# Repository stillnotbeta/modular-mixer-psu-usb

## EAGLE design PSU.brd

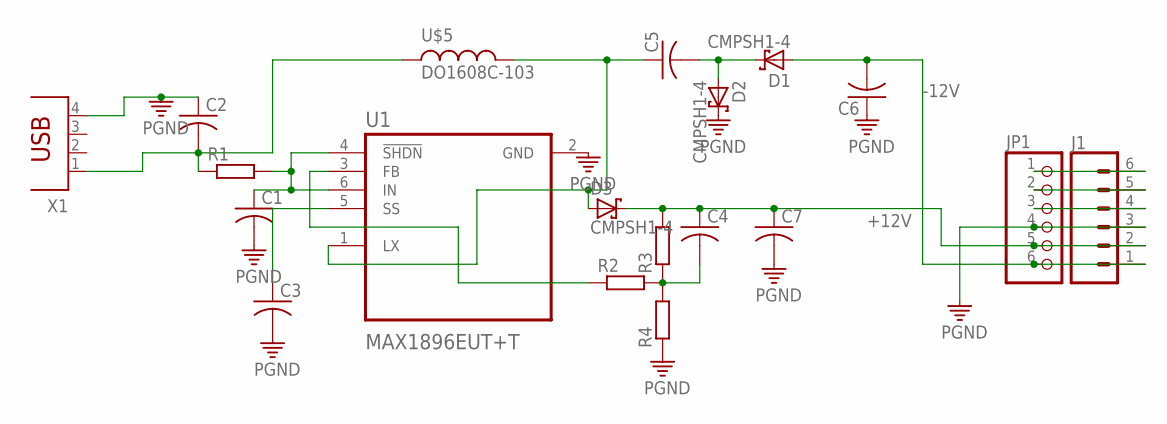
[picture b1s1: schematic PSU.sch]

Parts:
C1, C2, C3, C4, C5, C6, C7: C-US025-025X050; C025-025X050
D1, D2, D3: CMPSH1-4; SOT23
J1: CONN_06SMD-FEMALE-V2; 1X06-SMD-FEMALE
JP1: PINHD-1X6/90; 1X06/90
R1, R2, R3, R4: R-EU_0309/10; 0309/10
U1: MAX1896EUT+T; SOT95P280X145-6N
U$5: DO1608C-103; MSS1260
X1: PN61729

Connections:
+12V: C4.1, C7.1, D3.3 (C), J1.2, JP1.5, R3.2
-12V: C6.2, D1.1 (A), J1.1, JP1.6
unnamed: C1.1, R1.2, U1.4 (!SHDN), U1.6 (IN)
unnamed: C4.2, R2.2, R3.1, R4.2
unnamed: C2.2, R1.1, U$5.P$2, X1.1
unnamed: R2.1, U1.3 (FB)
unnamed: C5.1, D3.1 (A), U1.1 (LX), U$5.P$1
unnamed: C5.2, D1.3 (C), D2.1 (A)
unnamed: J1.4, JP1.3
unnamed: J1.5, JP1.2
unnamed: C3.1, U1.5 (SS)
unnamed: J1.6, JP1.1
PGND: C1.2, C2.1, C3.2, C6.1, C7.2, D2.3 (C), J1.3, JP1.4, R4.1, U1.2 (GND), X1.4

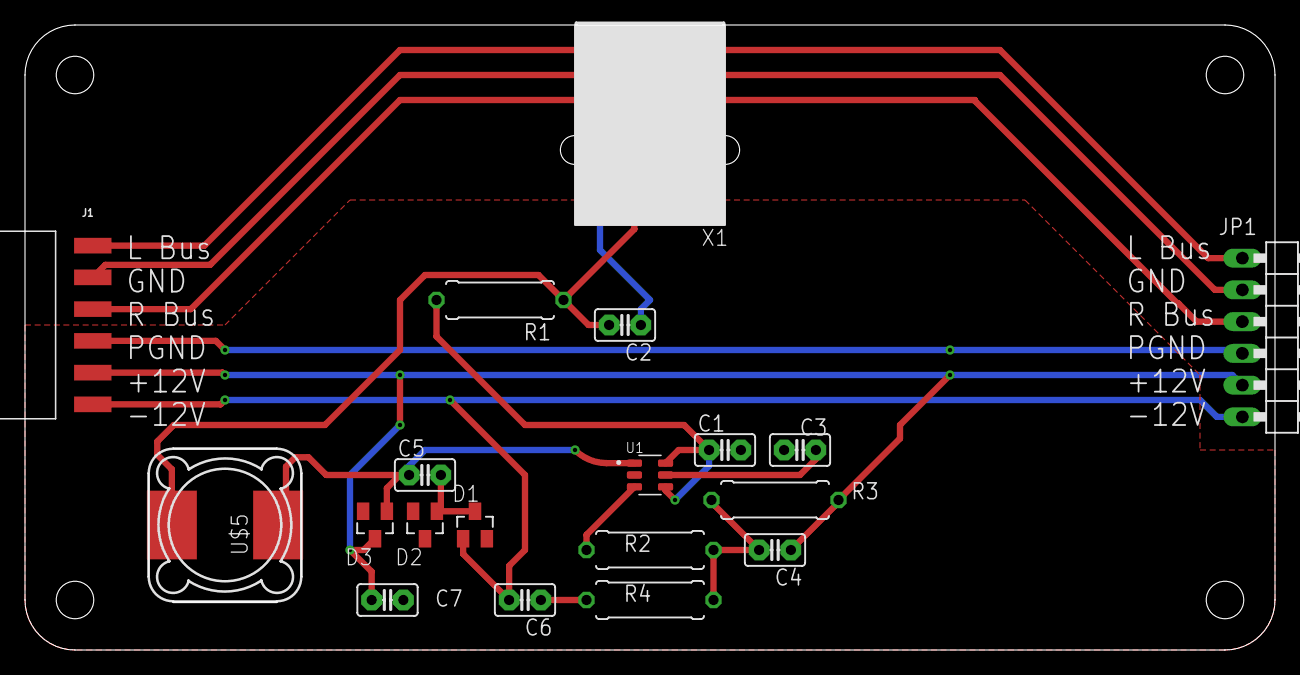
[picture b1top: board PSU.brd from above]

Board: 2 copper layers, 99.8 x 49.8 mm, 19 parts (0 on the bottom side), 13 nets.

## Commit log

2019-06-04 V 1.0
    These files have not been peer-reviewed and should NOT be manufactured.
2019-06-04 V 1.1
    These files have not been peer-reviewed and should NOT be manufactured.
    Changes: Added rounded corners, added connection between U1 Pin 6 and Pin 4
2019-06-12 V 1.1
    The first iteration of the PSU, we don't recommend to put these into production until they have been tested.

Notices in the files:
parts and their libraries:
SparkFun-Connectors: Licensing: Creative Commons ShareAlike 4.0 International - https://creativecommons.org/licenses/by-sa/4.0
